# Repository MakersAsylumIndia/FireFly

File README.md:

# FireFly
This circuit simulates a firefly with a tiny microcontroller. If put together with other fireflies, they will flash randomly. But after some time they will start to interact with each other and the flashes will start synchronize until all fireflies flash at once. Based on https://github.com/tinkerlog/fireflies

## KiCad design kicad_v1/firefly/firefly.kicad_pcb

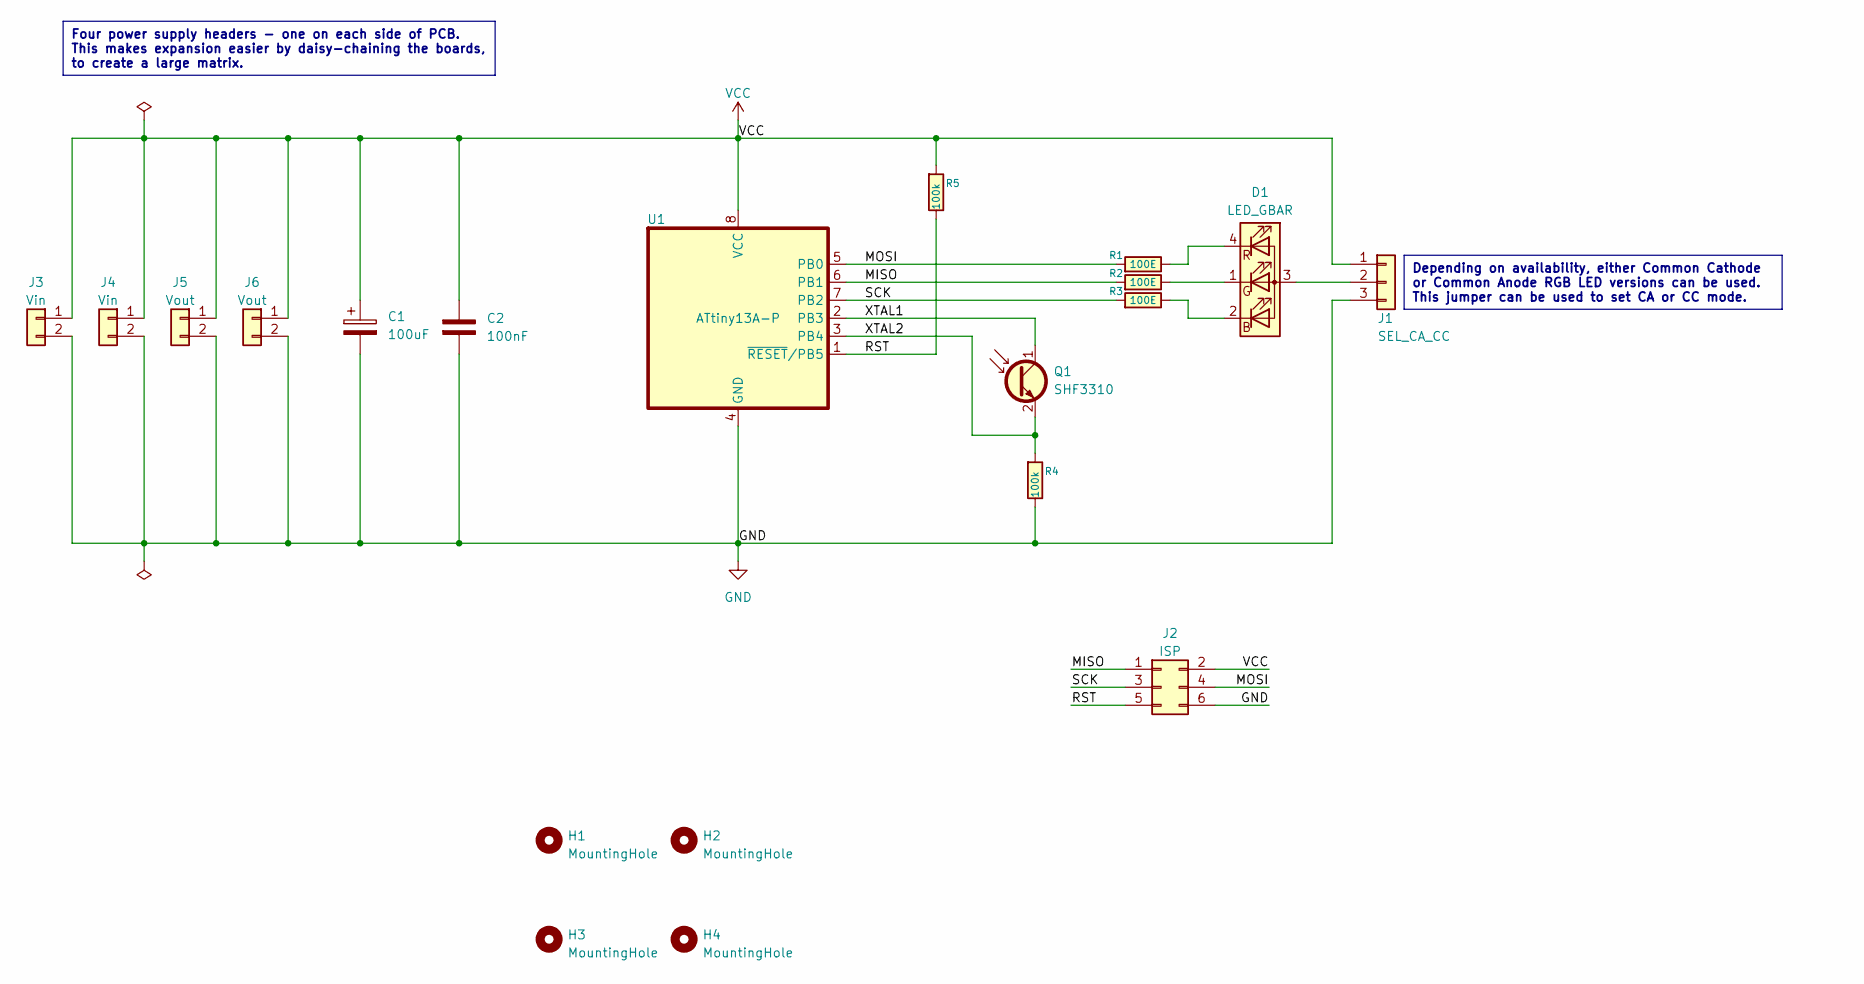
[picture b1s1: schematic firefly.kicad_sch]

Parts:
C1: 100uF; CP_Radial_D6.3mm_P2.50mm
C2: 100nF; C_Disc_D3.0mm_W2.0mm_P2.50mm
D1: LED_GBAR; LED_D5.0mm-4_RGB_square_Pins
H1, H2, H3, H4: MountingHole; MountingHole_3.2mm_M3_DIN965_Pad
J1: SEL_CA_CC; PinHeader_1x03_P1.00mm_Vertical
J2: ISP; PinHeader_2x03_P2.54mm_Vertical
J3, J4: Vin; PinHeader_1x02_P2.54mm_Vertical
J5, J6: Vout; PinHeader_1x02_P2.54mm_Vertical
Q1: SHF3310; LED_D5.0mm
R1, R2, R3: 100E; R_Axial_DIN0204_L3.6mm_D1.6mm_P7.62mm_Horizontal
R4, R5: 100k; R_Axial_DIN0204_L3.6mm_D1.6mm_P7.62mm_Horizontal
U1: ATtiny13A-P; DIP-8_W7.62mm_oval

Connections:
/MISO: J2.1, R2.1, U1.6 (PB1)
/MOSI: J2.4, R1.1, U1.5 (PB0)
/RST: J2.5, R5.2, U1.1 (~RESET/PB5)
/SCK: J2.3, R3.1, U1.7 (PB2)
/XTAL1: Q1.1 (C), U1.2 (PB3)
/XTAL2: Q1.2 (E), R4.1, U1.3 (PB4)
GND: C1.2, C2.2, J1.3, J2.6, J3.2, J4.2, J5.2, J6.2, R4.2, U1.4 (GND)
unnamed: D1.3 (A), J1.2
unnamed: D1.2 (BK), R3.2
unnamed: D1.1 (GK), R2.2
unnamed: D1.4 (RK), R1.2
VCC: C1.1, C2.1, J1.1, J2.2, J3.1, J4.1, J5.1, J6.1, R5.1, U1.8 (VCC)

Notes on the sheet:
Four power supply headers - one on each side of PCB. This makes expansion easier by daisy-chaining the boards, to create a large matrix.
Depending on availability, either Common Cathode or Common Anode RGB LED versions can be used. This jumper can be used to set CA or CC mode.

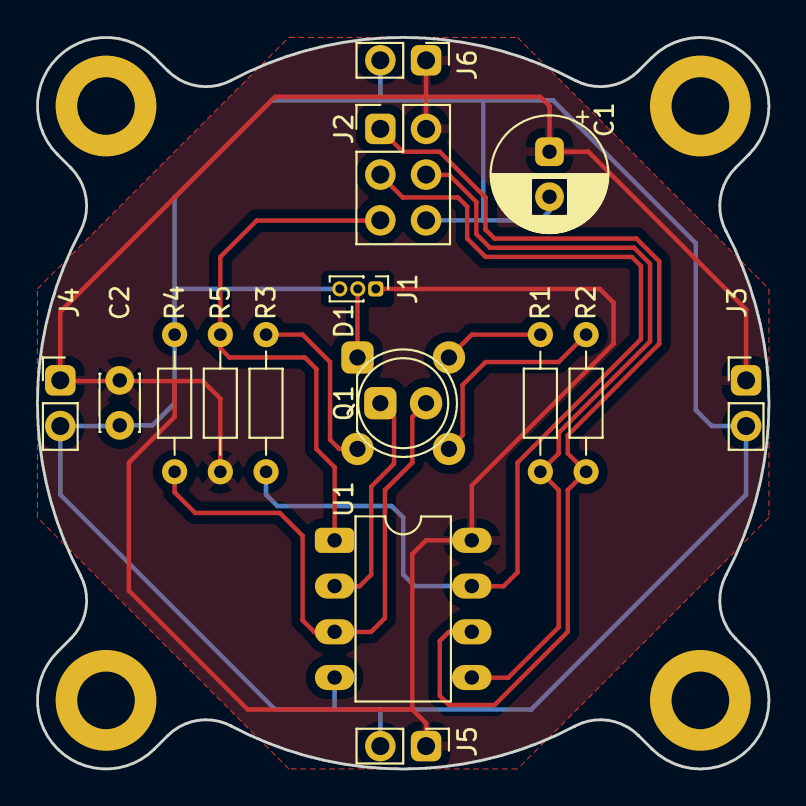
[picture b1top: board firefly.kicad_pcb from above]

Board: 2 copper layers, 40.6 x 40.6 mm, 20 parts (0 on the bottom side), 12 nets.

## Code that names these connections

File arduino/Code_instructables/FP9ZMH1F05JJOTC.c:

/* -----------------------------------------------------------------------
 * Title:    firefly
 * Author:   Alexander Weber <alexander.weber.0 at gmail.com>
 * Date:     18.03.2007
 * Hardware: ATtiny13v
 * Software: WinAVR 20060421
 */

// define as -D switch
//#define F_CPU 1200000	// clock 1.2MHz, internal oscillator

#include <avr/io.h>
#include <avr/eeprom.h>
#include <util/delay.h>

// use PB2 for led, pin 7
#define LED_BIT 2
// use PB3 to enable ldr, pin 2
#define ADC_ENA_BIT 3
// use ADC2, PB4, pin 3
#define CHANNEL 2
// power level
#define FLASH_POWER 8000
// daylight level
#define DAY_LIGHT 500

/*
 * get_adc
 * Return the 10bit value of the selected adc channel.
 */
uint16_t get_adc(uint8_t channel) {

	uint8_t i = 0;
	uint16_t value = 0;
	
	// enable voltage for LDR
	PORTB |= (1 << ADC_ENA_BIT);	
	
	// ADC setup
	ADCSRA = 
		(1 << ADEN) |						// enable ADC
		(1 << ADPS1) | (1 << ADPS0);		// set prescaler to 8	
		
	// select channel
	ADMUX = channel;
	
	// uncomment this to select reference voltage
	// ADMUX |= (1 << REFS0);	// use internal reference

	// warm up the ADC, discard the first conversion
	ADCSRA |= (1 << ADSC);
	while (ADCSRA & (1 << ADSC)); 
	
	// do 4 conversions and take the average
	for (i = 0; i < 4; i++) {				
		ADCSRA |= (1 << ADSC);				// start single conversion
		while (ADCSRA & (1 << ADSC)); 		// wait until conversion is done
		value += ADCW;
	}
	value = value >> 2;
		
	PORTB &= ~(1 << ADC_ENA_BIT);			// disable voltage for LDR
	ADCSRA &= ~(1<<ADEN); 					// shut down the ADC
		
	return value;
}



int main(void) {	
	
	uint8_t i = 0;
	uint16_t light = 0;
	uint16_t threshold = 0;
	uint16_t power = 0;
	uint8_t blind = 0;
	
	// define LED and ADC enable as outputs
	DDRB |= (1 << LED_BIT) |
			(1 << PB0) |
			(1 <<ADC_ENA_BIT);	
			
	// set pin 0 to low
	PORTB &= ~(1 << PB0);
	
	// intro
	for (i = 0; i < 5; i++) {
		PORTB |= (1 << LED_BIT);	
		_delay_ms(200);
		PORTB &= ~(1 << LED_BIT);
		_delay_ms(200);
	}
	
	// compute threshold
	for (i = 0; i < 4; i++) {
		threshold += get_adc(CHANNEL);
		_delay_ms(200);
		_delay_ms(200);
		_delay_ms(200);
		_delay_ms(200);
		_delay_ms(200);
	}	
	threshold = threshold >> 2;
	threshold += 80;

	while (1) {	
		
		_delay_loop_1(255);
		if (power > 6000) {
			power += 1;
		}
		else if (power > 4000) {
			power += 2;
		}
		else if (power > 3000) {
			power += 4;
		}
		else if (power > 2000) {
			power += 8;
		}
		else {
			power += 16;
		}

		if (!blind) {
		    light = get_adc(CHANNEL);
		    if (light > DAY_LIGHT) {				// if there is too much light
		    	for (i = 0; i < 20; i++) {			// then sleep some seconds
		    		_delay_ms(250);
		    	}
		    }
			else if (light > threshold) {			// if there was another flash then
				power += 200;						// increase power
				blind = 100;						// and we are blind for 100 cycles
			}
		}
		else if (blind > 0) {
			blind--;							
		}
						
		if (power > FLASH_POWER) {					// if there is enough power
			PORTB |= (1 << LED_BIT);				// flash on
			_delay_ms(200);							// for 0.2 seconds
			PORTB &= ~(1 << LED_BIT);				// flash off
			power = 0;
		}
		
	}

	return 0;
	
}

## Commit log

2023-04-18 initial commit for FireFly
2023-05-03 added code
